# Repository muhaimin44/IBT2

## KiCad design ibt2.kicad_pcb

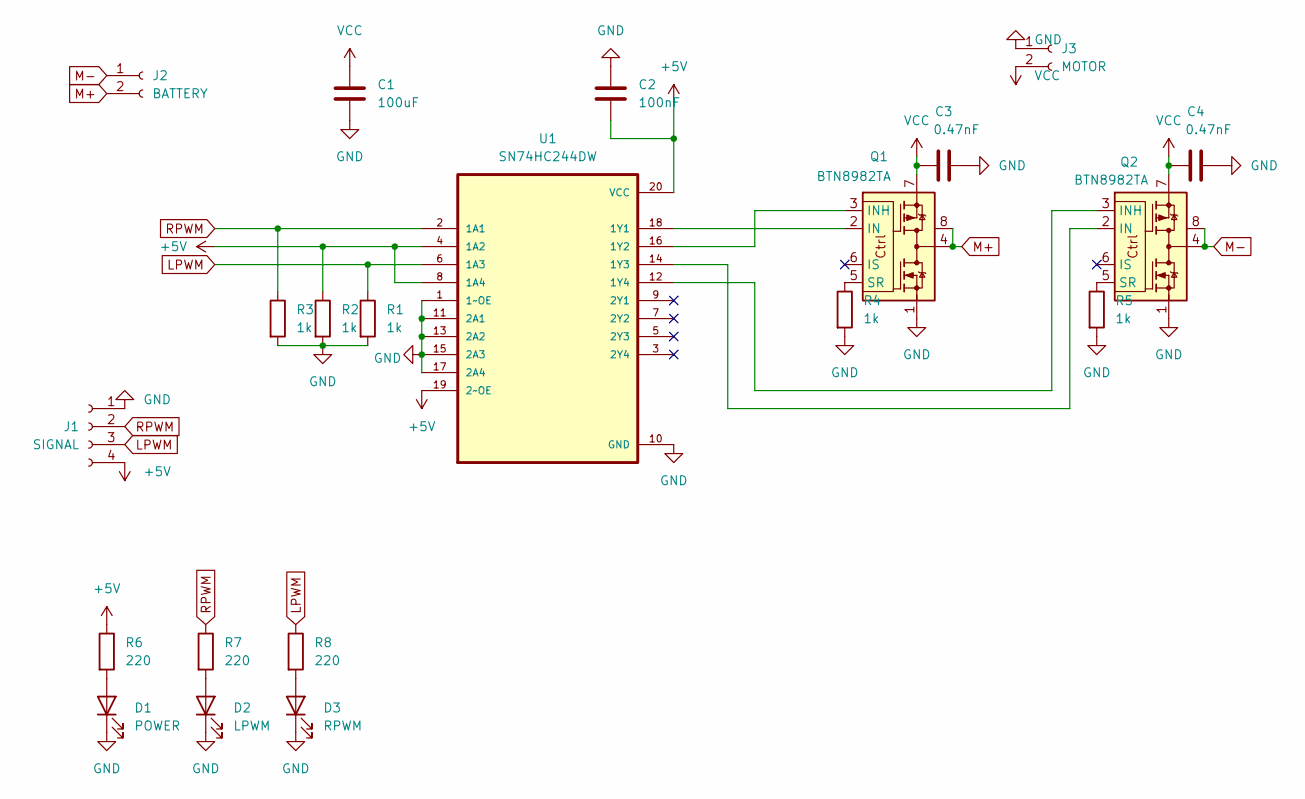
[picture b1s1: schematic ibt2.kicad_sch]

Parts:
C1: 100uF; CP_Radial_D10.0mm_P5.00mm
C2: 100nF; C_1206_3216Metric_Pad1.33x1.80mm_HandSolder
C3, C4: 0.47nF; C_1206_3216Metric_Pad1.33x1.80mm_HandSolder
D1: POWER; LED_D3.0mm
D2: LPWM; LED_D3.0mm
D3: RPWM; LED_D3.0mm
J1: SIGNAL; JST_XH_B4B-XH-A_1x04_P2.50mm_Vertical
J2: BATTERY; TerminalBlock_Phoenix_MKDS-1,5-2-5.08_1x02_P5.08mm_Horizont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
J3: MOTOR; TerminalBlock_Phoenix_MKDS-1,5-2-5.08_1x02_P5.08mm_Horizont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
Q1, Q2: BTN8982TA; TO-263-7_TabPin8
R1, R2, R3, R4, R5: 1k; R_1206_3216Metric_Pad1.30x1.75mm_HandSolder
R6, R7, R8: 220; R_Axial_DIN0207_L6.3mm_D2.5mm_P7.62mm_Horizontal
U1: SN74HC244DW; SOIC-20W_7.5x12.8mm_P1.27mm

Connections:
+5V: C2.2, J1.4, R2.1, R6.1, U1.4 (1A2), U1.8 (1A4), U1.19 (2~OE), U1.20 (VCC)
GND: C1.2, C2.1, C3.2, C4.2, D1.1 (K), D2.1 (K), D3.1 (K), J1.1, J3.1, Q1.1, Q2.1, R1.2, R2.2, R3.2, R4.2, R5.2, U1.1 (1~OE), U1.10 (GND), U1.11 (2A1), U1.13 (2A2), U1.15 (2A3), U1.17 (2A4)
LPWM: J1.3, R1.1, R8.1, U1.6 (1A3)
M+: J2.2, Q1.4, Q1.8
M-: J2.1, Q2.4, Q2.8
unnamed: D1.2 (A), R6.2
unnamed: D2.2 (A), R7.2
unnamed: D3.2 (A), R8.2
unnamed: Q1.2 (IN), U1.18 (1Y1)
unnamed: Q1.3 (INH), U1.16 (1Y2)
unnamed: Q1.5 (SR), R4.1
unnamed: Q2.2 (IN), U1.14 (1Y3)
unnamed: Q2.3 (INH), U1.12 (1Y4)
unnamed: Q2.5 (SR), R5.1
RPWM: J1.2, R3.1, R7.1, U1.2 (1A1)
VCC: C1.1, C3.1, C4.1, J3.2, Q1.7, Q2.7

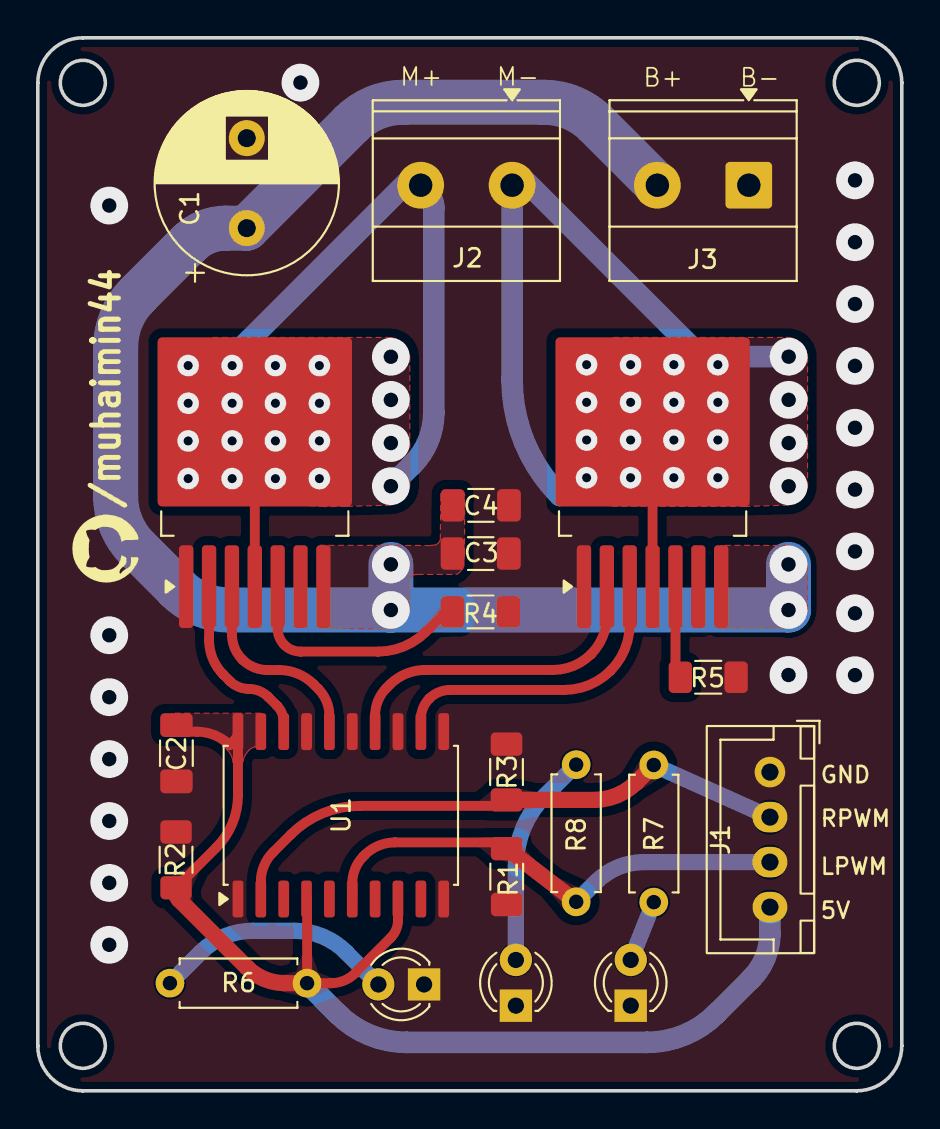
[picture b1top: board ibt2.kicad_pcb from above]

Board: 2 copper layers, 48.0 x 58.5 mm, 21 parts (0 on the bottom side), 16 nets.

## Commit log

2026-03-19 schematic done
